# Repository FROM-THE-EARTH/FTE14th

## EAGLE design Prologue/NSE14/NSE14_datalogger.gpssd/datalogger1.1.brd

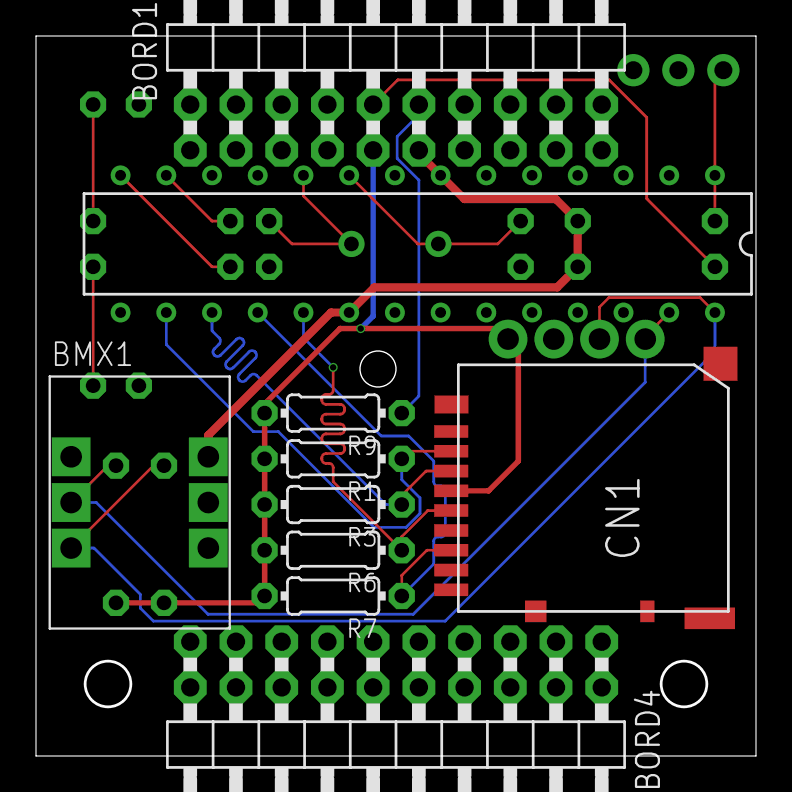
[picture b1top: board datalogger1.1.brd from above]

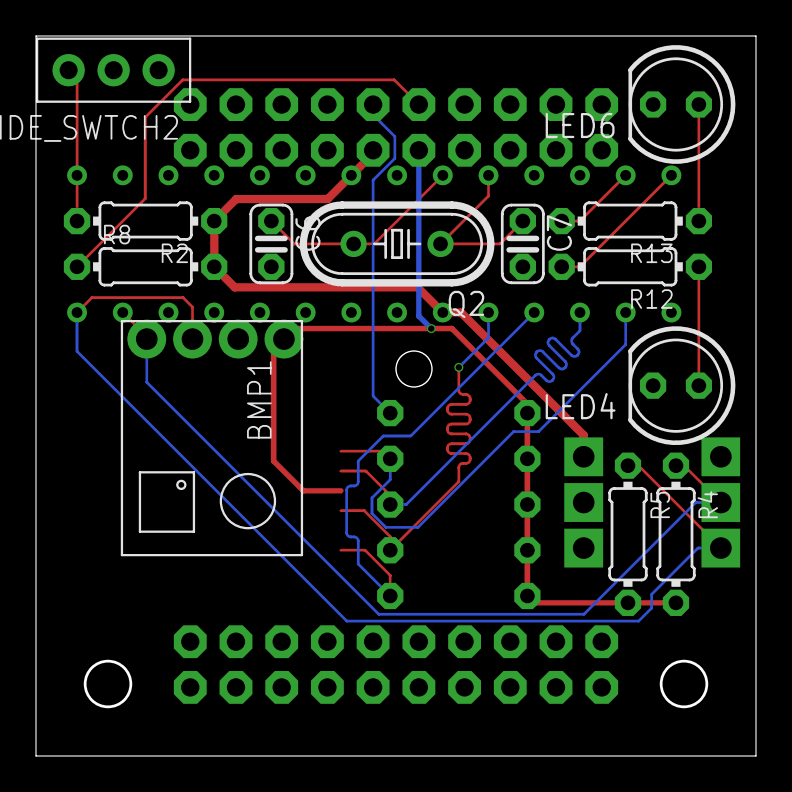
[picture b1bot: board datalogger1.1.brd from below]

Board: 2 copper layers, 40.0 x 40.0 mm, 23 parts (13 on the bottom side), 18 nets.

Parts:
BMP1: BMP180; GY-68
BMX1: BMX055
BORD1, BORD4: 2X10/90
C6, C7: 22p; C025-024X044
CN1: DM3AT
LED4, LED6: LED5MM
Q2: 16mhz; HC49/S
R1, R3, R4, R5, R6, R7: 10k; 0204/7
R2: 0204/7
R8, R9: 0; 0204/7
R12, R13: 100; 0204/7
SRIDE_SWTCH2: SRIDE_SWITCH
U$6: ATMEGA238P; ATMEGA328P

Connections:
+3V3: BMP1.P1, BORD1.9, CN1.VDD, R1.2, R3.2, R4.2, R5.2, R6.2, R7.2, R9.2
+5V: BMX1.VCC, BORD1.11, R2.1, R8.2, U$6.AVCC, U$6.VCC
CLK: CN1.CLK, R6.1, U$6.SCKD13
GND: BMP1.P2, BMX1.GND, BORD1.8, BORD1.13, C6.2, C7.2, CN1.VSS, LED4.K, LED6.K, SRIDE_SWTCH2.LR, U$6.GND1, U$6.GND2
LED1.0: R13.2, U$6.D7
LED1.1: R12.2, U$6.D8
unnamed: LED6.A, R13.1
unnamed: C6.1, Q2.2, U$6.PB6
unnamed: C7.1, Q2.1, U$6.PB7
unnamed: BORD1.10, R8.1
unnamed: LED4.A, R12.1
unnamed: R2.2, SRIDE_SWTCH2.R, U$6.RESET
unnamed: BORD1.12, R9.1
SCL: BMP1.P3, BMX1.SCL, R5.1, U$6.SCLD19
SD-MISO: CN1.DAT0, R7.1, U$6.MISOD12
SD-MOSI: CN1.CMD, R3.1, U$6.MOSID11
SD-SS: CN1.CD/DAT3, R1.1, U$6.SSD10
SDA: BMP1.P4, BMX1.SDA, R4.1, U$6.SDAD18

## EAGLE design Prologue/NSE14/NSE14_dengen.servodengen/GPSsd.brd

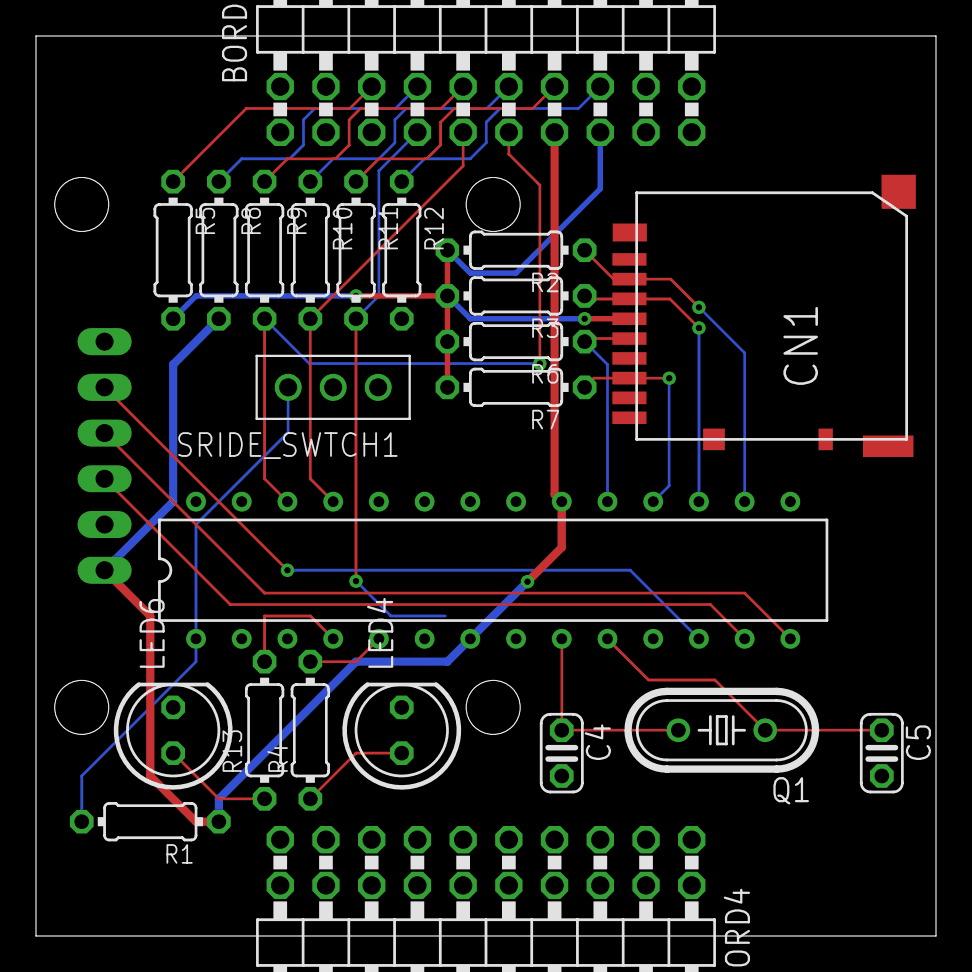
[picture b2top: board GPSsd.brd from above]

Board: 2 copper layers, 50.0 x 50.0 mm, 24 parts (1 on the bottom side), 26 nets.

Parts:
BORD1, BORD4: 2X10/90
C4, C5: 22p; C025-024X044
CN1: DM3AT
LED4, LED6: LED5MM
Q1: 16mhz; HC49/S
R1, R5, R8, R9, R10, R11, R12: 0204/7
R2, R3, R6, R7: 10k; 0204/7
R4, R13: 100; 0204/7
SRIDE_SWTCH1: SRIDE_SWITCH
U$1: ATMEGA238P; ATMEGA328P
U$2: NEWGPS

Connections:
+3V3: BORD1.15, CN1.VDD, R2.2, R3.2, R5.2, R6.2, R7.2
+5V: BORD1.13, R1.1, R8.2, U$1.AVCC, U$1.VCC, U$2.5V
BORDRX: BORD1.11, R9.2, U$1.D17
BORDTX: BORD1.9, R10.2, U$1.D16
CLK: CN1.CLK, R6.1, U$1.SCKD13
GND: BORD1.5, C4.2, C5.2, CN1.VSS, LED4.K, LED6.K, R12.2, SRIDE_SWTCH1.LR, U$1.GND1, U$1.GND2, U$2.GND
GPSRX: U$1.D7, U$2.TX
GPSTX: U$1.D8, U$2.RX
LED1.0: R13.2, U$1.D2
LED1.1: R4.2, U$1.D3
unnamed: LED6.A, R13.1
unnamed: BORD1.6, R5.1
unnamed: BORD1.8, R8.1
unnamed: BORD1.10, R9.1
unnamed: C5.1, Q1.1, U$1.PB7
unnamed: R1.2, SRIDE_SWTCH1.R, U$1.RESET
unnamed: C4.1, Q1.2, U$1.PB6
unnamed: BORD1.12, R10.1
unnamed: BORD1.14, R11.1
unnamed: BORD1.16, R12.1
unnamed: LED4.A, R4.1
RST: U$1.D6, U$2.RST
SD-MISO: CN1.DAT0, R7.1, U$1.MISOD12
SD-MOSI: CN1.CMD, R3.1, U$1.MOSID11
SD-SS: CN1.CD/DAT3, R2.1, U$1.SSD10
SERVO: BORD1.7, BORD4.10, BORD4.11, R11.2

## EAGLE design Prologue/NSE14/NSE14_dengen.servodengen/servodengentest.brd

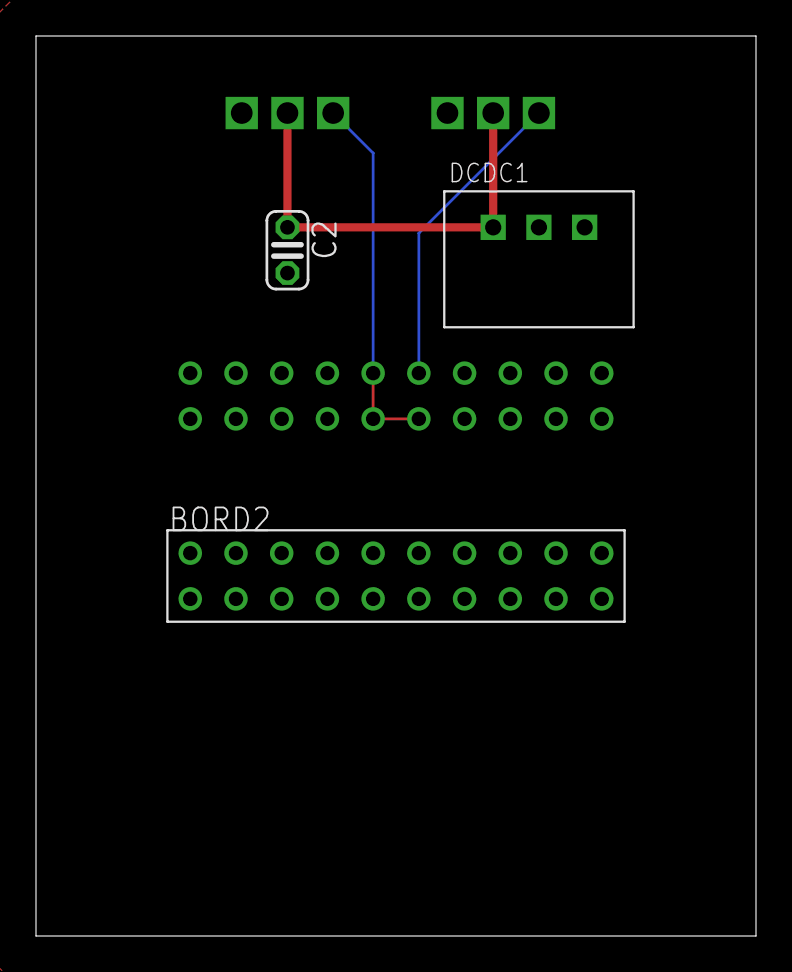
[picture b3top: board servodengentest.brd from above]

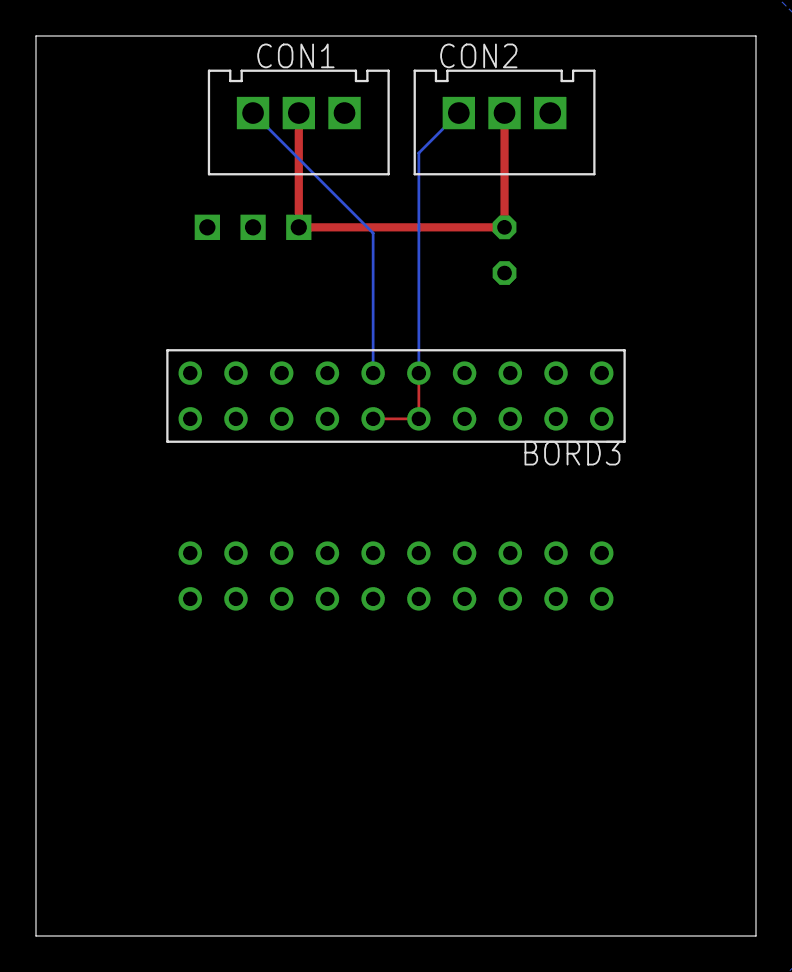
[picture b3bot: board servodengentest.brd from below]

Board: 2 copper layers, 40.0 x 50.0 mm, 6 parts (3 on the bottom side), 4 nets.

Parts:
BORD2, BORD3: 2X10
C2: 3.3uF; C025-024X044
CON1, CON2: 3PIN
DCDC1: 5V1A_M78AR05-1

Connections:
+5V: C2.1, CON1.P$2, CON2.P$2, DCDC1.VOUT
GND: C2.2, CON1.P$3, CON2.P$3, DCDC1.GND
SERVO1: BORD3.P$10, CON1.P$1
SERVO2: BORD3.P$9, BORD3.P$11, BORD3.P$12, CON2.P$1

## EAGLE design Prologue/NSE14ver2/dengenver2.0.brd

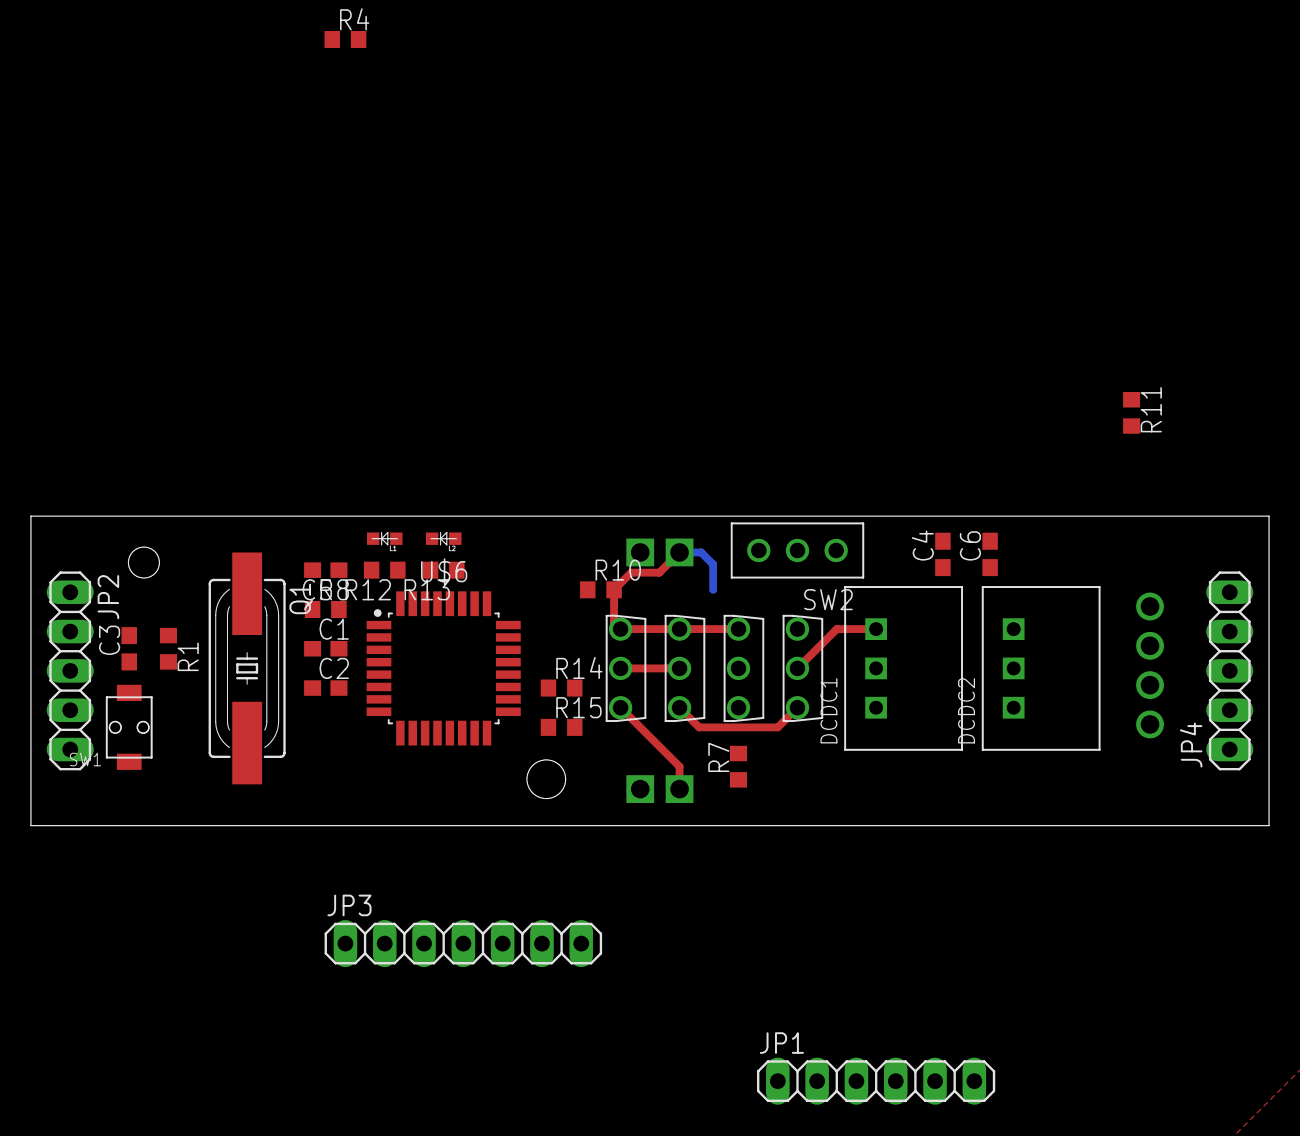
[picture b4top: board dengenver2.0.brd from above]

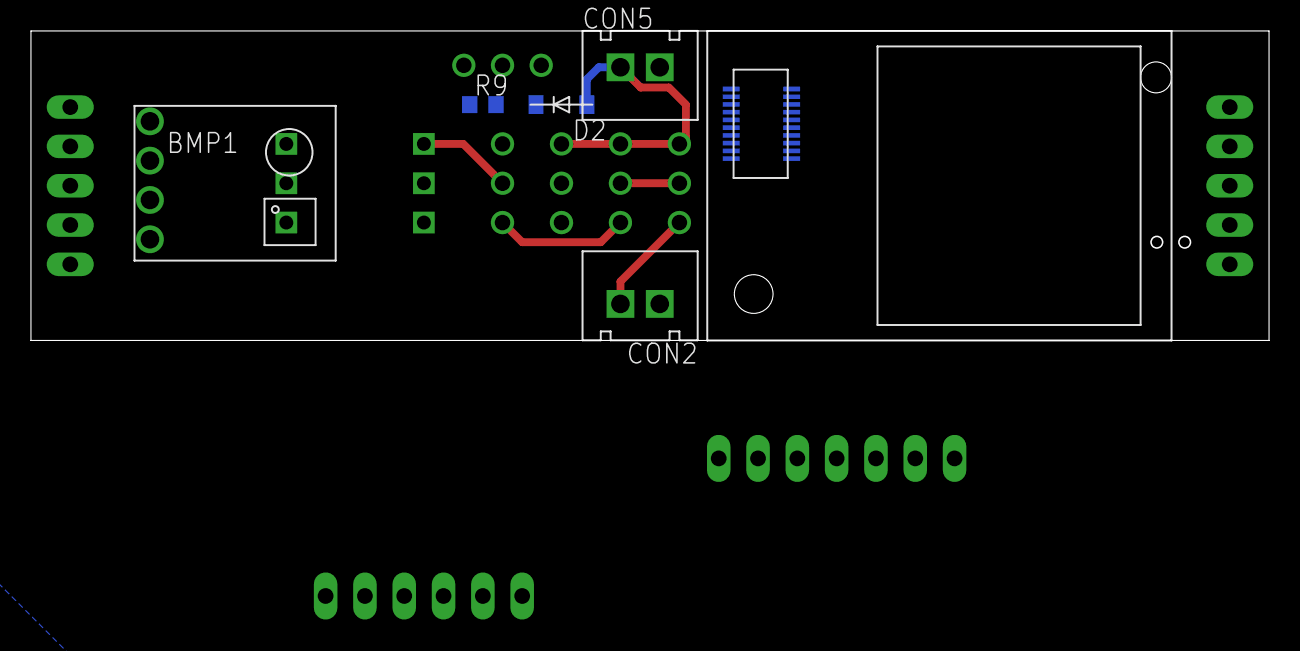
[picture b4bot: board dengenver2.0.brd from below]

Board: 2 copper layers, 80.0 x 20.0 mm, 38 parts (6 on the bottom side), 35 nets.

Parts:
BMP1: BMP180; GY-68
C1, C2: 22p; C1608
C3: 0.1μ; C1608
C4, C6: 3.3uF; C1608
C5: 10uF; C1608
CON2, CON5: 2PIN
D2: SOD-123
DCDC1: 5V1A_M78AR05-1
DCDC2: 3.3V1A_M78AR033-1
IM2: IM920_IM920C
JP1: 1X06
JP2, JP4: 1X05
JP3: 1X07
L1, L2: OSXX1608C1A
Q1: 16mhz; HC49UP
R1, R4, R7, R11: 10k; R0603
R8, R10: 1k; R0603
R9: 100k; R0603
R12, R13: 100; R0603
R14, R15: 4.7k; R0603
SW1: TVAF06-A020B-R
SW2: SRIDE_SWITCH
U$2, U$4, U$5: 2SJ681-PCH; 2SJ681
U$3: 2SK4017-NCH; 2SK4017
U$6: ATMEGA328P-AU; QFP80P900X900X120-32N

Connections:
+3V3: BMP1.P1, C6.1, DCDC2.VOUT, IM2.$P17, JP3.2, JP4.2, R4.2, R11.2, U$3.DRAIN
+5V: C4.1, DCDC1.VOUT, DCDC2.VIN, JP1.1, JP2.1, JP3.3, JP4.3, R1.1, R14.2, R15.2, U$6.AVCC, U$6.VCC1, U$6.VCC2
+5V1: DCDC1.VIN, U$5.DRAIN
BORD2: JP4.1, U$6.PB1
BORDRX: JP3.4, U$6.PC3
BORDTX: JP3.5, U$6.PC2
FP: CON5.P$1, D2.C, R10.2, U$2.GATE, U$3.GATE, U$4.GATE
FP_CHECKER: C5.1, R8.2, U$6.PD4
GND: BMP1.P2, C1.2, C2.2, C4.2, C5.2, C6.2, CON2.P$1, CON5.P$2, DCDC1.GND, DCDC2.GND, IM2.$P18, JP1.2, JP2.2, JP3.7, JP4.4, L1.CT, L2.CT, R7.1, R10.1, SW1.P$1, SW2.LR, U$6.GND1, U$6.GND2, U$6.GND3
IM_BUSY: IM2.$P1, U$6.PD6
IM_RESET: IM2.$P19, U$6.PD5
LED1.0: R13.2, U$6.PD2
LED1.1: R12.2, U$6.PD3
MISO: JP1.4, U$6.PB4
MOSI: JP1.5, U$6.PB3
unnamed: C2.1, Q1.2, U$6.PB7
unnamed: U$2.DRAIN, U$4.DRAIN
unnamed: D2.A, R9.2, U$4.SOURCE, U$5.SOURCE
unnamed: L2.AN, R13.1
unnamed: L1.AN, R12.1
unnamed: C1.1, Q1.1, U$6.PB6
unnamed: R7.2, R8.1, U$3.SOURCE
RAW: CON2.P$2, U$2.SOURCE
RESET: C3.2, JP2.3
RESETB: C3.1, JP1.6, R1.2, SW1.P$2, U$6.PC6
RX: JP2.4, U$6.PD0
RX_IM: IM2.$P6, U$6.PD7
SCK: JP1.3, U$6.PB5
SCL: BMP1.P3, R11.1, U$6.PC5
SDA: BMP1.P4, R4.1, U$6.PC4
SERVO: JP3.6, R14.1, U$6.PC1
SERVO2: JP3.1, R15.1, U$6.PC0
SW: R9.1, SW2.L, U$5.GATE
TX: JP2.5, U$6.PD1
TX_IM: IM2.$P7, U$6.PB0
